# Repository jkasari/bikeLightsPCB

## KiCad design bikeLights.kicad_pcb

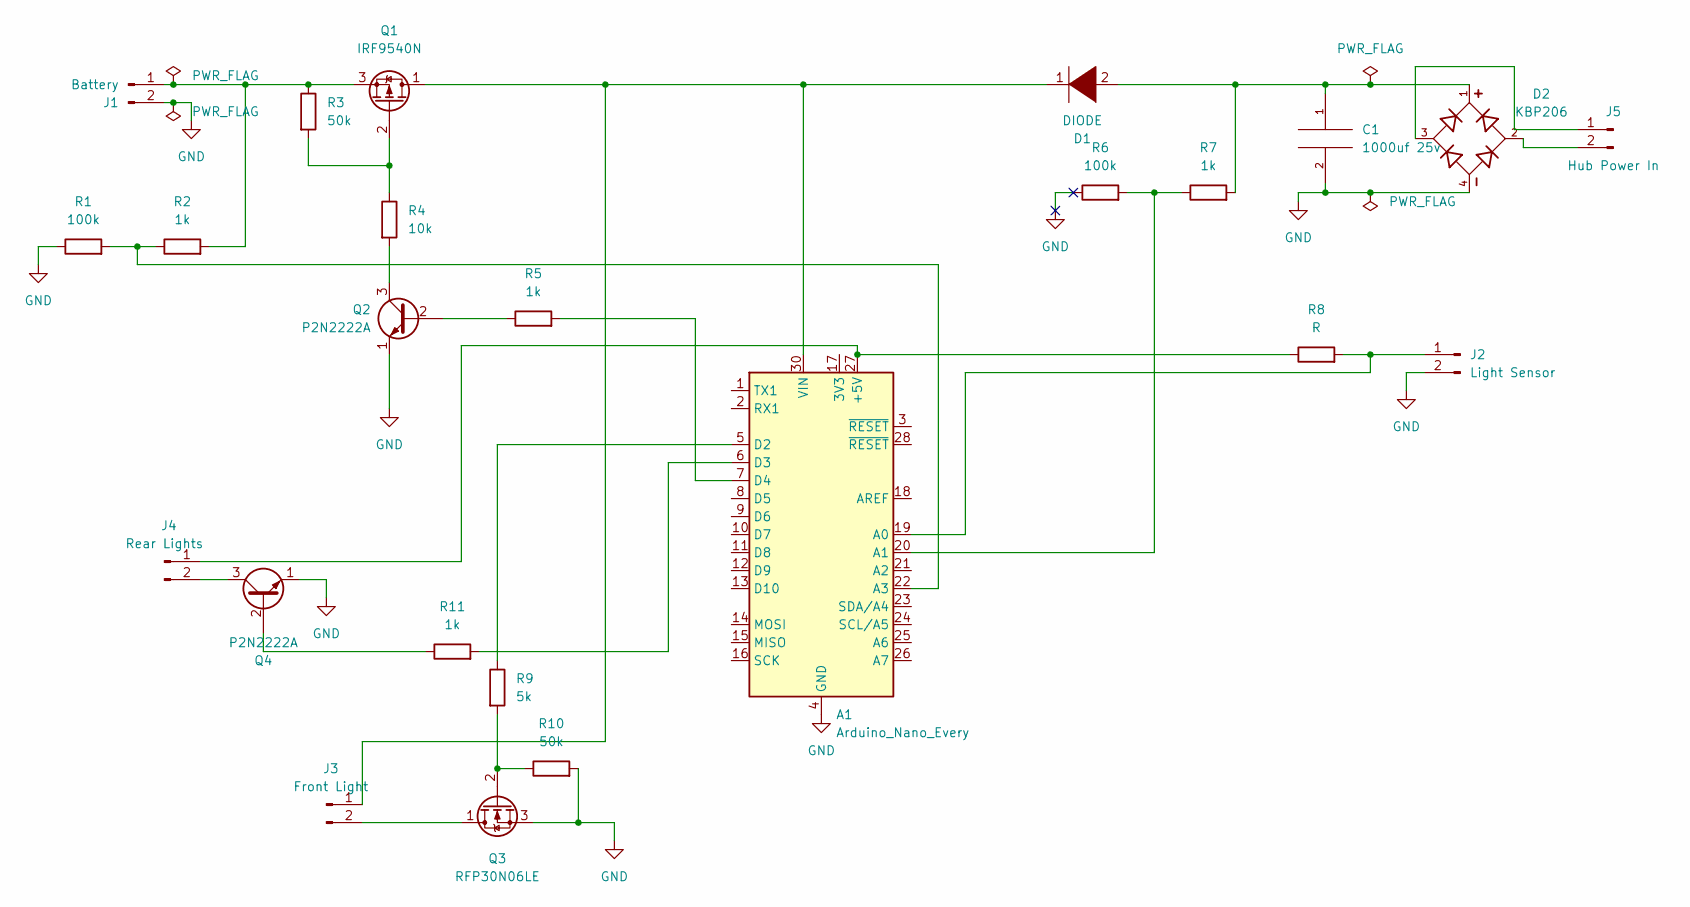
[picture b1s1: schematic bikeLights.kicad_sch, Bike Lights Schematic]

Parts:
A1: Arduino_Nano_Every; Arduino_Nano
C1: 1000uf 25v; CP_Radial_D10.0mm_P5.00mm
D1: DIODE; D_A-405_P10.16mm_Horizontal
D2: KBP206; SIP380W81P386L1470H1270Q4; PARTREV Oct. 2018
J1: Battery; solder_holes_medium
J2: Light Sensor; solder_holes_medium
J3: Front Light; solder_holes_medium
J4: Rear Lights; solder_holes_medium
J5: Hub Power In; solder_holes_medium
Q1: IRF9540N; mosfet_p_type_RFP30N6LE
Q2, Q4: P2N2222A; ON_Semi-CASE_2911-0-0-0
Q3: RFP30N06LE; mosfet_p_type_RFP30N6LE
R1, R6: 100k; R_Axial_DIN0309_L9.0mm_D3.2mm_P12.70mm_Horizontal
R2, R5, R7, R11: 1k; R_Axial_DIN0309_L9.0mm_D3.2mm_P12.70mm_Horizontal
R3, R10: 50k; R_Axial_DIN0309_L9.0mm_D3.2mm_P12.70mm_Horizontal
R4: 10k; R_Axial_DIN0309_L9.0mm_D3.2mm_P12.70mm_Horizontal
R8: R; R_Axial_DIN0309_L9.0mm_D3.2mm_P12.70mm_Horizontal
R9: 5k; R_Axial_DIN0309_L9.0mm_D3.2mm_P12.70mm_Horizontal

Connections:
GND: A1.4 (GND), A1.29 (GND), C1.2, D2.4, J1.2, J2.2, Q2.1 (E), Q3.3 (S), Q4.1 (E), R1.1, R6.1, R10.2
unnamed: A1.5 (D2), R9.1
unnamed: A1.6 (D3), R11.2
unnamed: A1.7 (D4), R5.2
unnamed: A1.19 (A0), J2.1, R8.2
unnamed: A1.20 (A1), R6.2, R7.1
unnamed: A1.22 (A3), R1.2, R2.1
unnamed: A1.27 (+5V), J4.1, R8.1
unnamed: A1.30 (VIN), D1.1 (A), J3.1, Q1.1 (D)
unnamed: C1.1, D1.2 (K), D2.1, R7.2
unnamed: D2.2, J5.2
unnamed: D2.3, J5.1
unnamed: J1.1, Q1.3 (S), R2.2, R3.1
unnamed: J3.2, Q3.1 (D)
unnamed: J4.2, Q4.3 (C)
unnamed: Q1.2 (G), R3.2, R4.1
unnamed: Q2.2 (B), R5.1
unnamed: Q2.3 (C), R4.2
unnamed: Q3.2 (G), R9.2, R10.1
unnamed: Q4.2 (B), R11.1

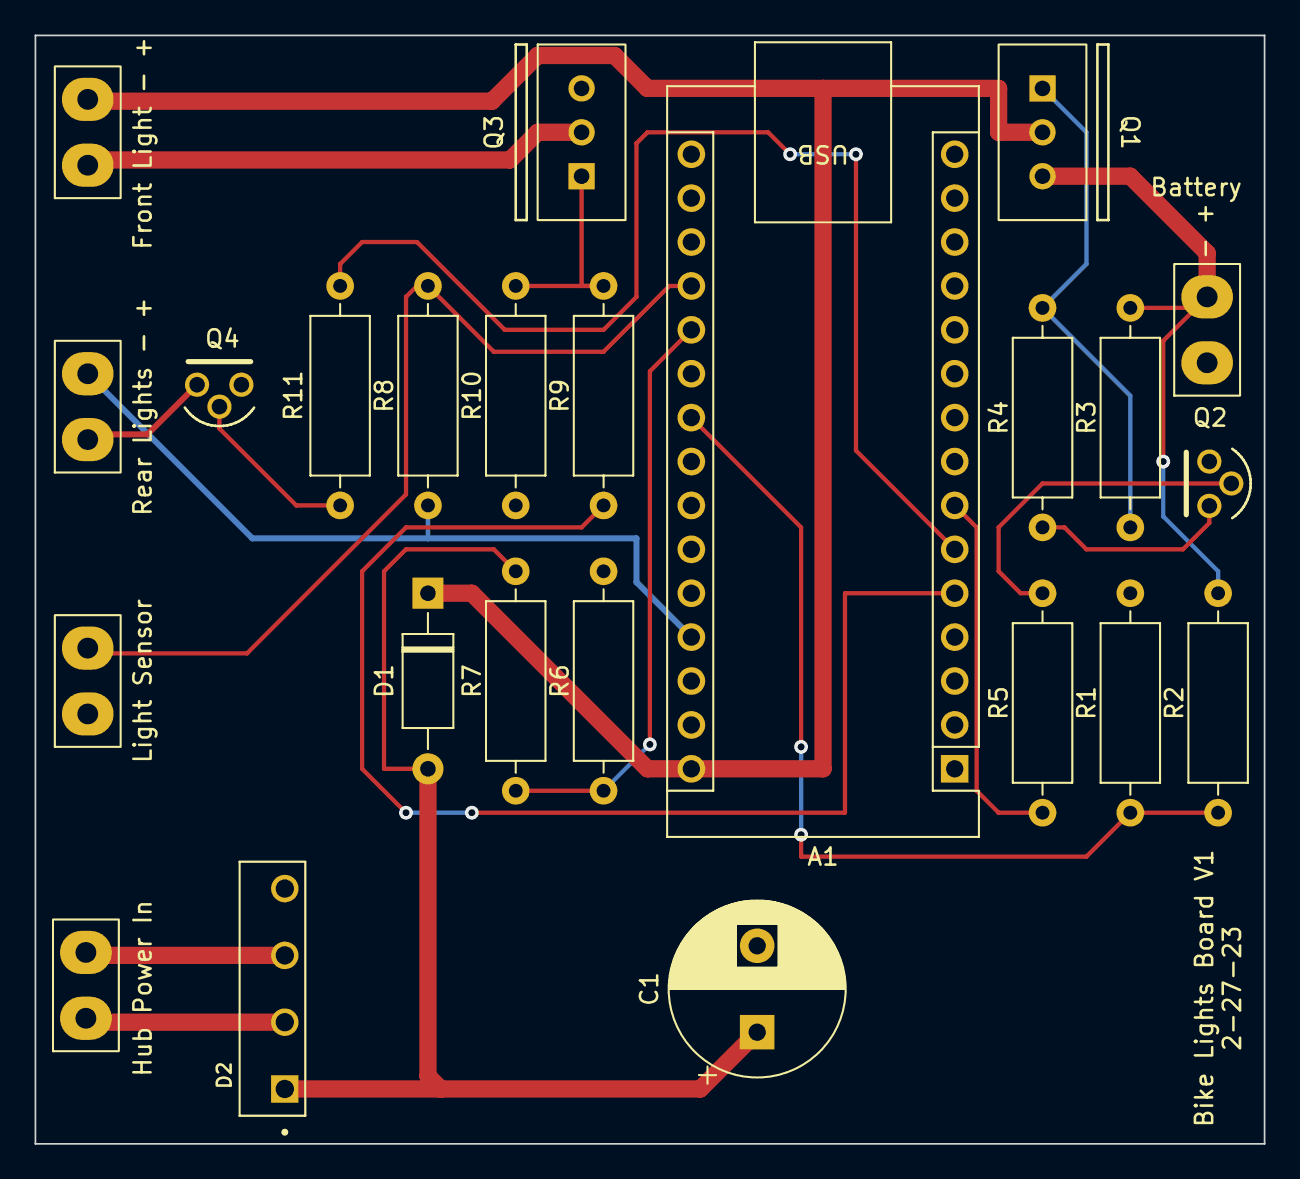
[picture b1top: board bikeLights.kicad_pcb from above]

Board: 2 copper layers, 71.1 x 64.1 mm, 24 parts (0 on the bottom side), 20 nets.

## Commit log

2023-02-28 First init
